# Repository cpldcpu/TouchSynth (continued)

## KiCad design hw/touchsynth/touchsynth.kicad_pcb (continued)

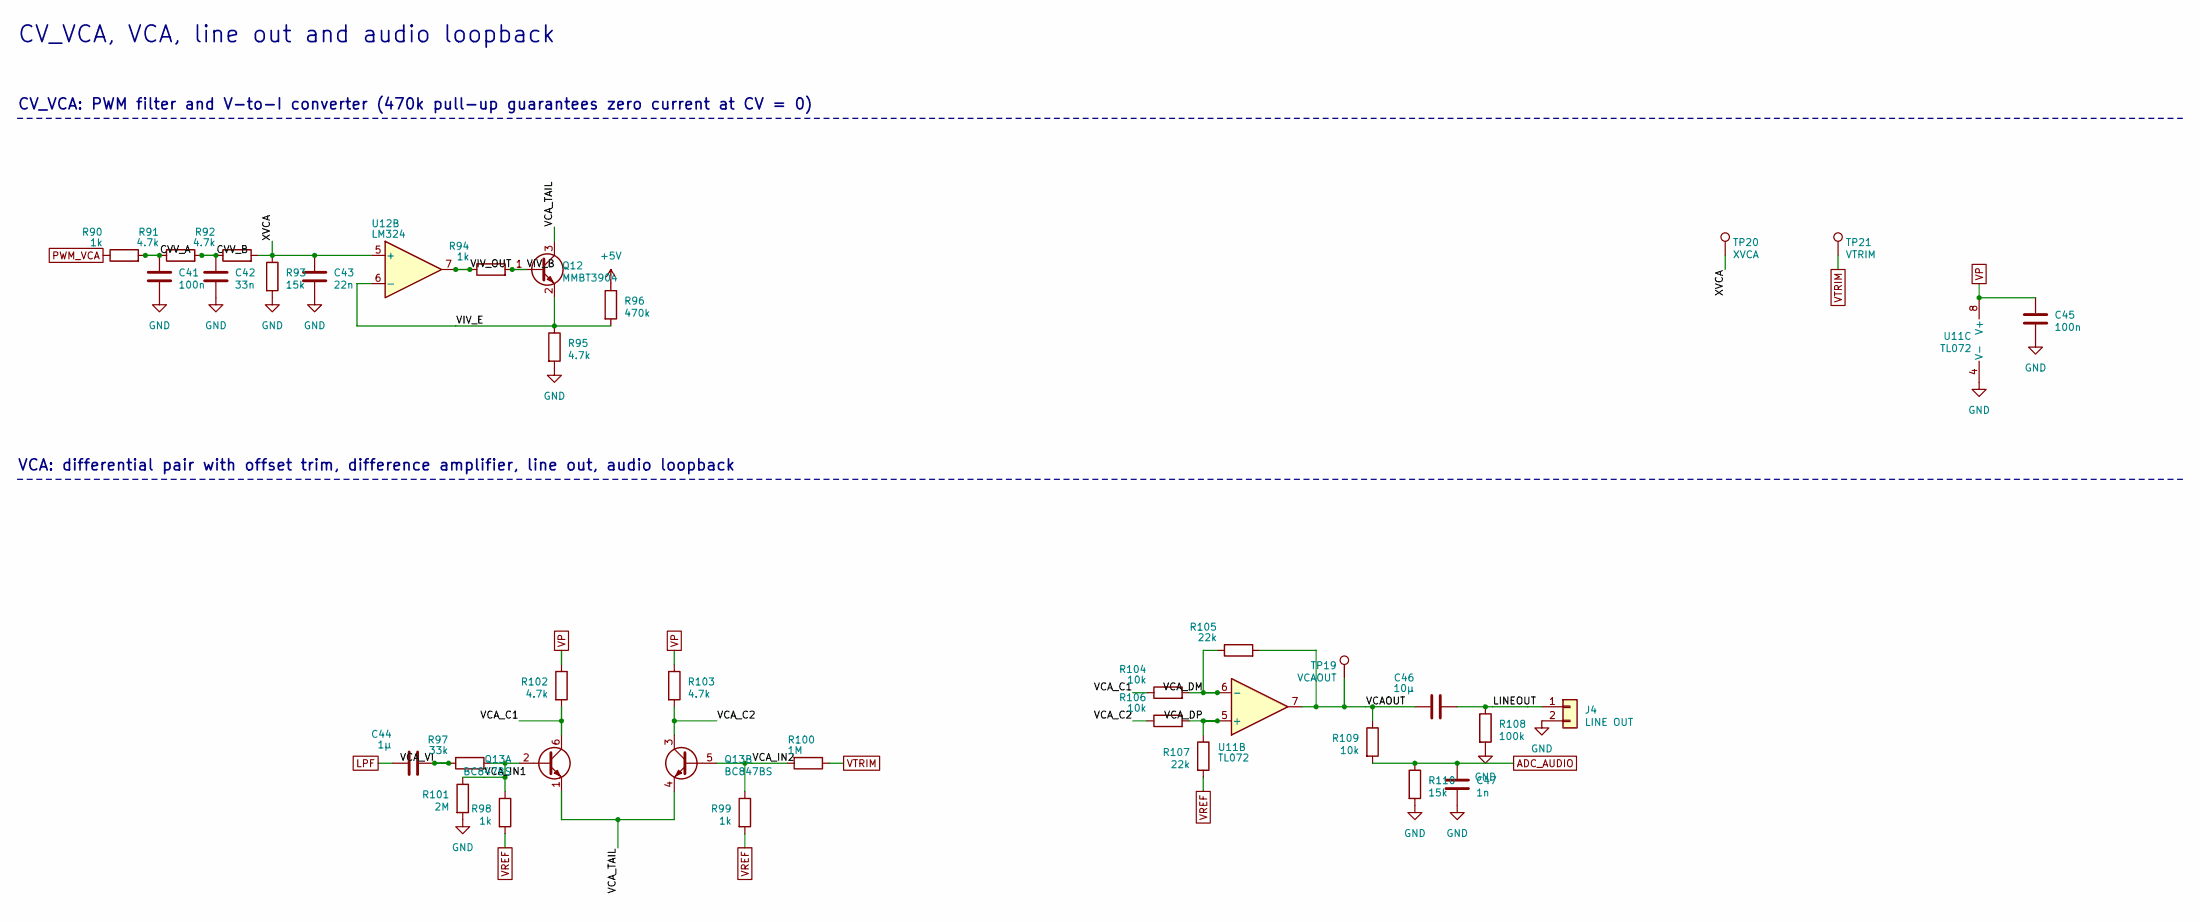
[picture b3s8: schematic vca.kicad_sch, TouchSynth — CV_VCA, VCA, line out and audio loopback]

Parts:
C41, C45: 100n; C_0603_1608Metric; LCSC C14663
C42: 33n; C_0603_1608Metric; LCSC C21117
C43: 22n; C_0603_1608Metric; LCSC C21122
C44: 1µ; C_0603_1608Metric; LCSC C15849
C46: 10µ; C_0603_1608Metric; LCSC C19702
C47: 1n; C_0603_1608Metric; LCSC C1588
J4: LINE OUT; PinHeader_1x02_P2.54mm_Vertical
Q12: MMBT3904; SOT-23; LCSC C20526
Q13: BC847BS; SOT-363_SC-70-6; LCSC C41375126
R90, R94, R98, R99: 1k; R_0603_1608Metric; LCSC C21190
R91, R92, R95, R102, R103: 4.7k; R_0603_1608Metric; LCSC C23162
R93, R110: 15k; R_0603_1608Metric; LCSC C22809
R96: 470k; R_0603_1608Metric; LCSC C23178
R97: 33k; R_0603_1608Metric; LCSC C4216
R100: 1M; R_0603_1608Metric; LCSC C22935
R101: 2M; R_0603_1608Metric; LCSC C22976
R104, R106, R109: 10k; R_0603_1608Metric; LCSC C25804
R105, R107: 22k; R_0603_1608Metric; LCSC C31850
R108: 100k; R_0603_1608Metric; LCSC C25803
TP19: VCAOUT; TestPoint_Pad_D1.0mm
TP20: XVCA; TestPoint_Pad_D1.0mm
TP21: VTRIM; TestPoint_Pad_D1.0mm
U11: TL072; SOIC-8_3.9x4.9mm_P1.27mm; LCSC C6961
U12: LM324; SOIC-14_3.9x8.7mm_P1.27mm; LCSC C71035

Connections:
+5V: R96.1; also elsewhere on the board
/vca/CVV_A: C41.1, R90.2, R91.1
/vca/CVV_B: C42.1, R91.2, R92.1
/vca/LINEOUT: C46.2, J4.1, R108.1
/vca/VCAOUT: C46.1, R105.2, R109.1, TP19.1, U11.7
/vca/VCA_C1: Q13.6 (C1), R102.2, R104.1
/vca/VCA_C2: Q13.3 (C2), R103.2, R106.1
/vca/VCA_DM: R104.2, R105.1, U11.6 (-)
/vca/VCA_DP: R106.2, R107.1, U11.5 (+)
/vca/VCA_IN1: Q13.2 (B1), R97.2, R98.1, R101.1
/vca/VCA_IN2: Q13.5 (B2), R99.1, R100.2
/vca/VCA_TAIL: Q12.3 (C), Q13.1 (E1), Q13.4 (E2)
/vca/VCA_VI: C44.2, R97.1
/vca/VIV_B: Q12.1 (B), R94.2
/vca/VIV_E: Q12.2 (E), R95.1, R96.2, U12.6 (-)
/vca/VIV_OUT: R94.1, U12.7
/vca/XVCA: C43.1, R92.2, R93.1, TP20.1, U12.5 (+)
ADC_AUDIO: C47.1, R109.2, R110.1; also elsewhere on the board
GND: C41.2, C42.2, C43.2, C45.2, C47.2, J4.2, R93.2, R95.2, R101.2, R108.2, R110.2, U11.4 (V-); also elsewhere on the board
LPF: C44.1; also elsewhere on the board
PWM_VCA: R90.1; also elsewhere on the board
VP: C45.1, R102.1, R103.1, U11.8 (V+); also elsewhere on the board
VREF: R98.2, R99.2, R107.2; also elsewhere on the board
VTRIM: R100.1, TP21.1; also elsewhere on the board

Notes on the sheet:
CV_VCA, VCA, line out and audio loopback
CV_VCA: PWM filter and V-to-I converter (470k pull-up guarantees zero current at CV = 0)
VCA: differential pair with offset trim, difference amplifier, line out, audio loopback

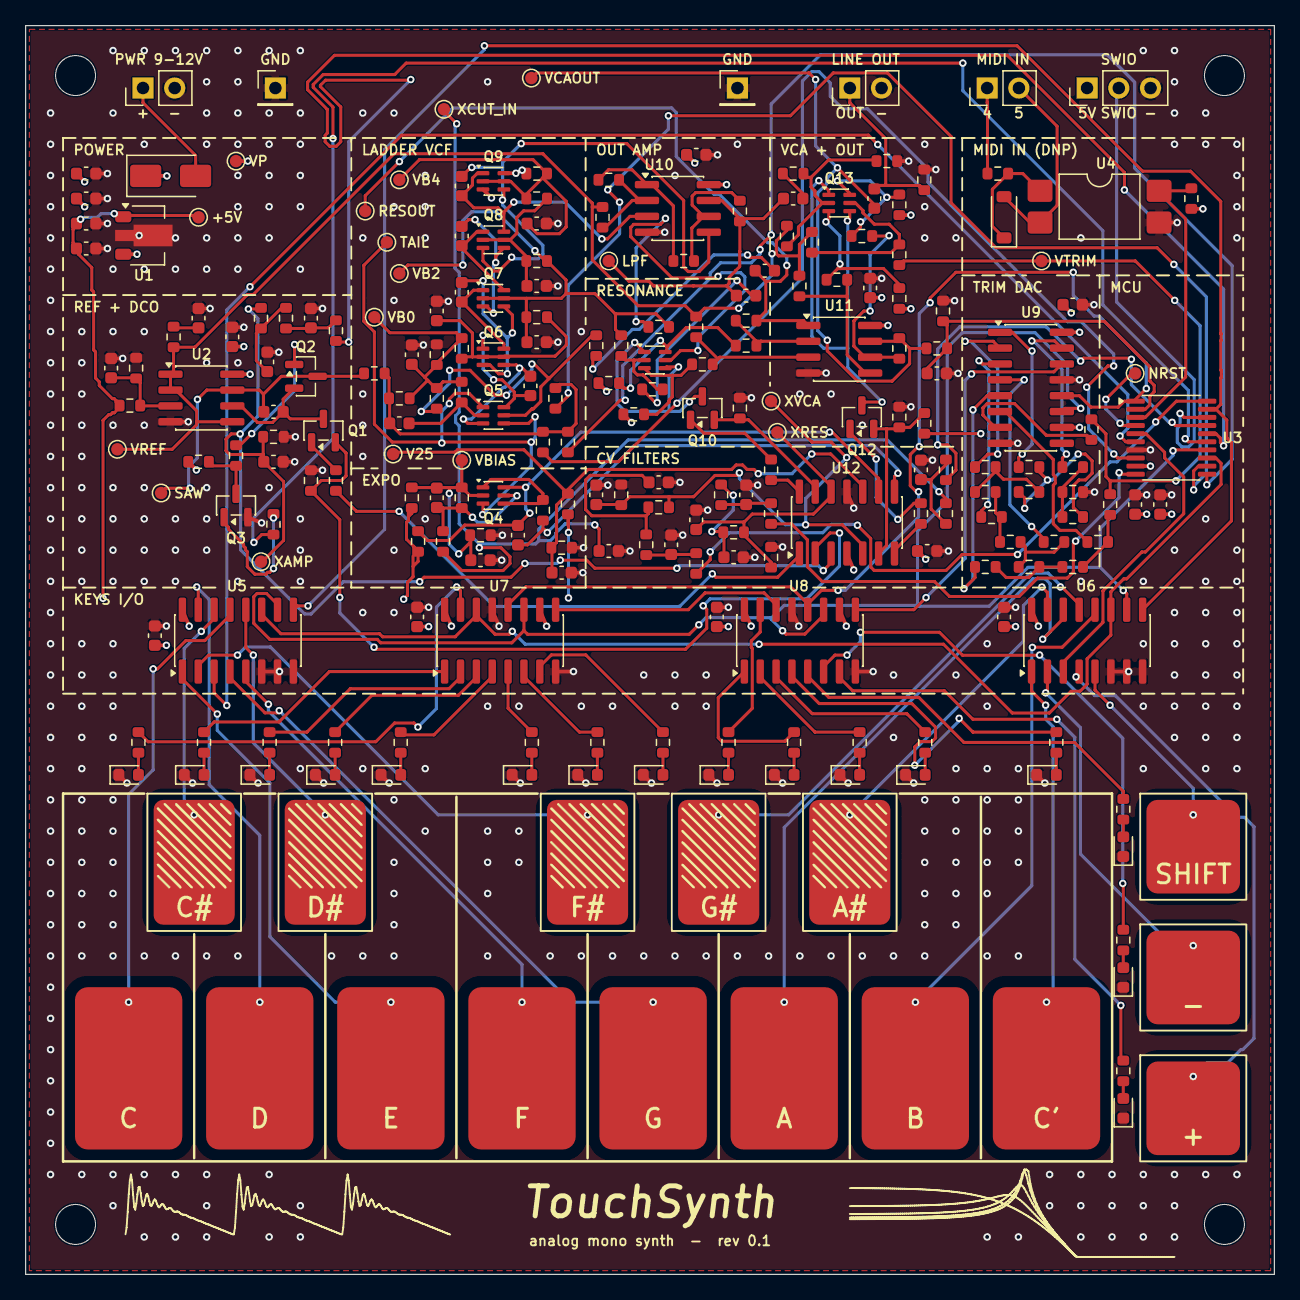
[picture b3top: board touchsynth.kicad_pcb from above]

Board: 4 copper layers, 100.0 x 100.0 mm, 246 parts (0 on the bottom side), 166 nets.

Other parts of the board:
H1, H2, H3, H4: M3; MountingHole_3.2mm_M3

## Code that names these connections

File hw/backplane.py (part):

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POWER = {"GND": "power:GND", "+5V": "power:+5V", "+3V3": "power:+3V3"}
RAIL = "+5V_IN"                                 # always a global label (input rail ahead of the slot rail)
FLAG_SHEETS = {"power": ("GND", "VBUS_C", "+5V_EXT", "+5V_IN", "+5V"),   # PWR_FLAGs: supplies no power-output
               "mcu": ("VDDA",), "mixer": ("VA_MIX",)}                 # pin drives (+3V3: LDO, VBUS_HOST: U4)
FLAGS = sum(FLAG_SHEETS.values(), ())
LAYOUTS = "layouts_backplane"                   # hand-drawn sheet layouts (power, mcu, bus, mixer)
SLOTS = 8
FX_SLOT = 1                    # the effects slot (pins 15 / 14 switchable to the mix sends, end of file)

SHEETS = OrderedDict([
    ("power", "Power entry, 3.3 V, soft start (option), USB-C device port, USB-A host port"),
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    pins = {}
    for k, (a, b) in enumerate(pairs):
        pins[1 + k], pins[8 - k] = a, b
    return add("RN", "Device:R_Pack04", value, FP["RN4"], pins, lcsc=lcsc, note=note)


def LED(color, a, k, note, **kw):
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

def HDR(ref, n, value, pins, note=None, dnp=False):
    return add("J", f"Connector_Generic:Conn_01x{n:02d}", value, FP[f"HDR{n}"], dict(enumerate(pins, 1)), ref=ref,
               bom=False, note=note, dnp=dnp)


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# =========================================================================== controller
sheet("mcu")
group("CH32V203C8T6 (assembled), decoupling, reset")
MCU = {1: "+3V3", 2: "SR_LATCH", 3: "SR_OE_N", 4: "PC15", 5: "OSC_IN", 6: "OSC_OUT", 7: "MCU_NRST", 8: "GND",
       9: "VDDA", 10: "ADC_L", 11: "ADC_R", 18: "PB0", 19: "CLK_O", 20: "LED_ACT", 21: "BCAST_O", 22: "RETURN",
       23: "GND", 24: "+3V3", 27: "PB14", 28: "VBUS_DET", 29: "SYNC_O", 30: "UART_TX", 31: "UART_RX",
       32: "USBD_DM", 33: "USBD_DP", 34: "SWDIO", 35: "GND", 36: "+3V3", 37: "SWCLK", 38: "FLASH_CS_N",
       39: "SPI_SCK", 40: "SPI_MISO", 41: "SPI_MOSI", 42: "USBH_DM", 43: "USBH_DP", 44: "BOOT0", 45: "HOST_EN",
       46: "HOST_FLT_N", 47: "GND", 48: "+3V3"}
SWIO_PIN = {1: 12, 2: 13, 3: 14, 4: 15, 5: 16, 6: 17, 7: 25, 8: 26}     # PA2 ... PA7, PB12, PB13
MCU.update({pin: f"SWIO_{k}" for k, pin in SWIO_PIN.items()})
add("U", "MCU_WCH_RiscV:CH32V203CxTx", "CH32V203C8T6", FP["LQFP48"], MCU, ref="U1", lcsc="C3001172",
    note="assembled by JLCPCB (C3001172, Extended; from the user's JLCPCB personal stock); SPI1 remap 1 (PA15/PB3/PB4/PB5); TIM3 CH4 (PB1) = 24 MHz CLK option")
for pin in (24, 36, 48):
    C(None, "100n", "+3V3", "GND", 3.3, note=f"MCU decoupling VDD pin {pin}")
C(None, "100n", "+3V3", "GND", 3.3, note="MCU decoupling VBAT")
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add("JP", "Jumper:Jumper_3_Open", "BOOT0", FP["HDR3"], {1: "+3V3", 2: "BOOT0", 3: "GND"}, ref="JP2", bom=False,
    note="1-2: system bootloader (USART1 / USB), open or 2-3: run from flash")
R(None, "10k", "BOOT0", "GND", note="BOOT0 low by default")
HDR("J6", 3, "UART", ("GND", "UART_TX", "UART_RX"), note="USART1: GND, TX (PA9), RX (PA10); 5 V adapters are fine (FT)")
group("MIDI DIN in (option, not fitted): opto into PA10 through JP3")
HDR("J7", 3, "MIDI IN", ("MIDI_4", "MIDI_5", "GND"), note="DIN pin 4, DIN pin 5, shield (panel jack on wires)",
    dnp=True)
R(None, "220", "MIDI_4", "MIDI_LA", dnp=True, note="MIDI loop series")
add("U", "Isolator:LTV-817S", "LTV-817S", FP["OPTO"], {1: "MIDI_LA", 2: "MIDI_5", 3: "GND", 4: "MIDI_RX"},
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R(None, "10k", "FLASH_CS_N", "+3V3", note="flash deselected while the MCU boots")
R(None, "10k", "FLASH_WP_N", "+3V3", note="flash WP idle")
R(None, "10k", "FLASH_HOLD_N", "+3V3", note="flash HOLD idle")
R(None, "10k", "LED_ACT", "GND", note="PB2 = BOOT1: low at reset")
R(None, "1k", "LED_ACT", "LED_ACT_A", note="activity LED series")
LED("yellow", "LED_ACT_A", "GND", "activity")
for n in ("PC15", "PB0", "PB14"):
    TP(n, note="free MCU pin")
for n in ("+3V3", "+5V", "GND"):
    TP(n)
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# other slot; a voice card grounds them, which these not-fitted positions ignore) into the line-out stage
# instead of the mix (loop-through: remove the line-out 220 R from MIX_L / MIX_R, fit the two below).
sheet("bus")
group("Effects slot 1: pins 15 / 14 = CLK / SWIO_1 or the mix sends; pins 3 / 4 = the loop-through return")
R(None, "0", "CLK", "FX_P15", note="effects slot: CLK to slot 1 pin 15 (remove for an effects card)")
R(None, "220", "MIX_L", "FX_P15", dnp=True, note="effects slot: send L to slot 1 pin 15 (fit for an effects card)")
R(None, "0", "SWIO_1", "FX_P14", note="effects slot: SWIO_1 to slot 1 pin 14 (remove for an effects card)")
R(None, "220", "MIX_R", "FX_P14", dnp=True, note="effects slot: send R to slot 1 pin 14 (fit for an effects card)")
R(None, "220", "FX_RET_L", "LO_L", dnp=True, note="effects slot: return L from slot 1 pin 3 to the line out (loop-through)")
R(None, "220", "FX_RET_R", "LO_R", dnp=True, note="effects slot: return R from slot 1 pin 4 to the line out (loop-through)")

# --------------------------------------------------------------------------- simulation cross-reference (S12 --bus2)
SIM_ONLY = {f"{e}{x}{s}_0".upper() for e in ("RO", "LO", "CC", "RBC") for x in "lr" for s in range(SLOTS)} | \
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
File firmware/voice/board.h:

/* TouchSynth board definition: pins from hw/design.py (MCU U3, TSSOP-20), remap codes per chip family.
 *
 *  pin port  net          use                         pin port  net          use
 *   1  PD4   LATCH        74HC595 RCLK (GPIO)          11  PC1   SUB          sub-oscillator (GPIO)
 *   2  PD5   ADC_AUDIO    ADC IN5 <- audio loopback    12  PC2   PULSE        TIM2 CH2
 *   3  PD6   MIDI_RX      USART1 RX                    13  PC3   S0_DATA      mux S0 / 595 SER
 *   4  PD7   NRST                                      14  PC4   S1_CLK       mux S1 / 595 SRCLK
 *   5  PA1   TOUCH_B      mux B common, ADC IN1        15  PC5   DCO_RST      TIM2 CH1 (active low)
 *   6  PA2   TOUCH_A      mux A common, ADC IN0        16  PC6   PWM_AMP      TIM1 CH1
 *   8  PD0   NOISE        noise (GPIO)                 17  PC7   PWM_CUT      TIM1 CH2
 *  10  PC0   PWM_RES      TIM1 CH3                     18  PD1   SWIO
 *                                                       19  PD2   S2           mux S2 (GPIO)
 *                                                       20  PD3   PWM_VCA      TIM1 CH4
 *
 * Timer remaps (checked against the CH32V003 reference header and the CH32V002 datasheet pin table):
 *   CH32V003: TIM1 partial remap 1 (01b): CH1 PC6, CH2 PC7, CH3 PC0, CH4 PD3
 *             TIM2 partial remap 1 (01b): CH1 PC5, CH2 PC2
 *   CH32V00x: TIM1_RM = 0010b: TIM1_CH1_2 PC6, TIM1_CH2_2 PC7, TIM1_CH3_2 PC0, TIM1_CH4_2 PD3
 *             TIM2_RM = 010b:  TIM2_CH1_ETR_2 PC5, TIM2_CH2_2 PC2
 * The complementary / break functions these remaps also route (TIM1 CH1N PC3, CH2N PC4, CH3N PD1, BKIN PC1,
 * TIM2 CH3 PD2) are never enabled; TIM2 CH4 on PC1 only in the dual-PWM DAC build (DAC_DUAL, hw.h).
 */
#ifndef BOARD_H
#define BOARD_H

#include "ch32fun.h"

#ifndef BOARD_CARD
#define BOARD_CARD 0                                   /* 1: the voice card (make BOARD=card), else board 1 */
#endif

#if BOARD_CARD
/* Voice card (hw/voice.py, docs/spec.md 3.2; TSSOP-20 pin numbers, the same port pins on any V006 package):
 *   PD4 SYNC_IN (EXTI)   PD5 TX_OUT (bus return)   PD6 RX_IN (bus)   PD0 LED_PLAY   PC3 LED_STAT
 *   PC6 TIM1 CH1 VCA trim   PC7 CH2 CV_CUT   PC0 CH3 CV_RES   PD3 CH4 CV_VCA   PC2 TIM2 CH2 DAC   PC1 TIM2 CH4 DAC low
 *   PC4 ADC A2 loopback   PA2 A0 / PD2 A3 self-test (option)   PA1 clock in (option)   PC5 spare
 * No DCO, no 74HC595: CV channel 0 is the VCA trim, hw_leds_dac() drives the two LEDs and the trim. */
#define PIN_SYNC     PD4
#define PIN_TX       PD5
#define PIN_MIDI_RX  PD6                               /* bus RX */
#define PIN_LED_PLAY PD0
#define PIN_LED_STAT PC3
#define PIN_CV_AMP   PC6                               /* CV channel 0: VCA trim on the card */
#define PIN_CV_CUT   PC7
#define PIN_CV_RES   PC0
#define PIN_CV_VCA   PD3
#define PIN_PULSE    PC2                               /* DAC */
#define PIN_SUB      PC1                               /* DAC low byte (dual PWM) */
#define PIN_AUDIO    PC4
#define ADC_CH_AUDIO 2
#else
#define PIN_LATCH    PD4
#define PIN_AUDIO    PD5
#define PIN_MIDI_RX  PD6
#define PIN_TOUCH_B  PA1
#define PIN_TOUCH_A  PA2
#define PIN_NOISE    PD0
#define PIN_CV_RES   PC0
#define PIN_SUB      PC1
#define PIN_PULSE    PC2
#define PIN_S0_DATA  PC3
#define PIN_S1_CLK   PC4
#define PIN_DCO_RST  PC5
#define PIN_CV_AMP   PC6
#define PIN_CV_CUT   PC7
#define PIN_S2       PD2
#define PIN_CV_VCA   PD3

#define ADC_CH_TOUCH_A 0
#define ADC_CH_TOUCH_B 1
#define ADC_CH_AUDIO   5
#endif

#if defined(CH32V003)
#define CHIP_NAME "CH32V003"
#define REMAP_MASK   (AFIO_PCFR1_TIM1_REMAP | AFIO_PCFR1_TIM2_REMAP)
#define REMAP_BITS   (AFIO_PCFR1_TIM1_REMAP_PARTIALREMAP1 | AFIO_PCFR1_TIM2_REMAP_PARTIALREMAP1)
#elif defined(CH32V00x)
#if defined(CH32V002)
#define CHIP_NAME "CH32V002"
#elif defined(CH32V006)
#define CHIP_NAME "CH32V006"
#else
#define CHIP_NAME "CH32V00x"
#endif
#define REMAP_MASK   (AFIO_PCFR1_TIM1_RM | AFIO_PCFR1_TIM2_RM)
#define REMAP_BITS   (AFIO_PCFR1_TIM1_RM_1 | AFIO_PCFR1_TIM2_RM_1)       /* TIM1_RM = 0010b, TIM2_RM = 010b */
#else
#error "unsupported MCU"
#endif

/* timer register bits (identical on both families; the vendor headers name them differently) */
#define T_CEN      0x0001
#define T_UDIS     0x0002
#define T_ARPE     0x0080
#define T_CMS2     0x0040   /* centre-aligned mode 2 (counts up and down, compare flags on the up-count only) */
#define T_UIE      0x0001
#define T_UIF      0x0001
#define T_UDE      0x0100   /* DMAINTENR: DMA request on update */
#define T_CC1DE    0x0200   /* DMAINTENR: CC1 DMA request */
#define T_CCDS     0x0008   /* CTLR2: the CCx DMA requests at the update event */
#define T_UG       0x0001
#define T_MOE      0x8000
#define T_OC_PWM1_LO  0x0068   /* OCxM = 110 (PWM1) + OCxPE, channel 1 / 3 half of CHCTLRx */
#define T_OC_PWM1_HI  0x6800   /* same for channel 2 / 4 */
#define T_OC_FRZ_LO   0x0008   /* OCxM = 000 (frozen: compare flag only) + OCxPE, channel 1 / 3 */
#define T_CC1E     0x0001
#define T_CC1P     0x0002
#define T_CC2E     0x0010
#define T_CC3E     0x0100
#define T_CC4E     0x1000

#define F_CPU      48000000UL
#define RESET_TICKS 144        /* DCO reset pulse: 3 us at 48 MHz (same as RESET_COUNTS in tables.h) */
#define CV_PWM_TOP 1023        /* TIM1: 10 bit at 46.875 kHz, 2 more bits by dithering */
#define FRAME_CYCLES 48000     /* HCLK cycles per 1 ms frame (SYNC period), nominal */
#ifndef BUS_BAUD
#define BUS_BAUD   1000000     /* card: voice bus (docs/bus.md 2): USART divider 48 = 3.0 (2 Mbaud: 24 = 1.5, exact) */
#endif
#ifndef BUS_TX_PP
#define BUS_TX_PP  0           /* 1: drive the return line push-pull during a reply (bench without pull-up, hw.c) */
#endif

/* interrupt state save / restore (mstatus.MIE only), usable in the control tick as well as in the main loop:
   ch32fun's __disable_irq / __enable_irq also clear / set MPIE, which inside a handler changes the state that mret
   restores */
static inline uint32_t irq_save(void)
{
	uint32_t s;
	__asm volatile(ADD_ARCH_ZICSR "csrrci %0, mstatus, 8" : "=r"(s) :: "memory");
	return s;
}

static inline void irq_restore(uint32_t s)
{
	if (s & 8)
		__asm volatile(ADD_ARCH_ZICSR "csrsi mstatus, 8" ::: "memory");
}

#endif

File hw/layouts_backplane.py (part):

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# drawn as global labels like the cross-sheet nets around them, so the label stacks stay uniform: on the bus sheet
# the bus nets at the slot sockets, on the MCU sheet the local nets at the controller and flash pins
GLOBAL = {"SYNC", "BCAST", "CLK", "FX_P14", "FX_P15", "FX_RET_L", "FX_RET_R"} | {f"NRST_{k}" for k in range(1, D.SLOTS + 1)} | \
    {"PC15", "PB0", "PB14", "LED_ACT", "BOOT0", "SPI_MISO", "FLASH_CS_N", "FLASH_WP_N", "FLASH_HOLD_N"}
PART = {p.ref: p for p in D.PARTS}


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

def tp(net, k=0):
    return [p.ref for p in D.PARTS if p.lib_id == "Connector:TestPoint" and p.pins["1"] == net][k]


def by(pred):
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def nets(**pins):
    """the part whose pins carry exactly these nets (pin number -> net), e.g. nets(_1="CC1", _2="GND")"""
    want = {k.lstrip("_"): v for k, v in pins.items()}
    return by(lambda p: p.pins == want)


def vcap(sh, r, x, ytop, gnd=True, fields="right"):
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    # ESD array on the connector side of the 0 R positions
    u3 = "U3"
    sh.place(u3, 76.2, 132.08, fields=(15.24, -13.97))
    for pin, net, d in ((1, "USBC_DM", (-1, 0)), (3, "USBC_DP", (-1, 0)), (4, "CC1", (1, 0)), (6, "CC2", (1, 0))):
        stub(sh, (u3, pin), d, net)
    vp = sh.P(u3, 5)
    sh.w(vp, (vp[0], vp[1] - U), (vp[0] + 7.62, vp[1] - U))
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    u5 = "U5"
    sh.place(u5, 177.8, yh + 17.78, fields=(-20.32, -10.16))
    sh.w((u5, 5), (177.8, yh))
    for pin, net in ((1, "USBH_DM"), (3, "USBH_DP")):
        stub(sh, (u5, pin), (-1, 0), net)
    sh.gnd((u5, 2))
    # D-, D+ pull-down options
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    vcap(sh, note("reset filter"), rs[0] - 17.78, yr)
    sh.text("RESET: the controller only; the 595", rs[0] - 50.8, yr + 20.32, 1.27, False)
    sh.text("outputs go off, the cards keep running", rs[0] - 50.8, yr + 24.13, 1.27, False)
    sh.text("SPI1 remap 1 (PA15, PB3, PB4, PB5); TIM3 CH4 (PB1) = 24 MHz CLK option", xm - 50.8, ym + 60.96, 1.27,
            False)

    # ---- crystal
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    sh.text("X50328MSB2GI: 20 pF load, 2 x 30 pF with the strays", 66.04, yy + 22.86, 1.27, False)

    # ---- MIDI DIN in (option)
    sh.heading("MIDI DIN in (option, not fitted): opto into PA10 through JP3", 15, 30, 137)
    X, Y = 83.82, 60.96
    sh.place("U9", X, Y, fields="above")
    sh.place("J7", 25.4, Y, mirror="y", fields="left")            # pins on the right
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    sh.lbl((clk[0] + 33.02, clk[1]), "SWCLK", (1, 0))
    v33(sh, stub_w(sh, sh.P("J5", 1), -U, horiz=True))
    sh.gnd(stub_w(sh, sh.P("J5", 4), -U, horiz=True))
    sh.text("J6 USART1: GND, TX (PA9), RX (PA10); 5 V adapters are fine (FT pins)", 289.56, 118.11, 1.27, False)
    sh.text("J5 WCH-LinkE: 3V3, SWDIO, SWCLK, GND", 289.56, 152.4, 1.27, False)
    # BOOT0 jumper
    yb0 = 177.8
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        r = nets(_1=net, _2="+3V3")
        sh.place(r, xp + i * 10.16, yp + 3.81, 180, fields="right")     # pin 2 (+3V3) up
        sh.lbl((r, 1), net, (0, 1), stub=U)
    # activity LED on PB2 (= BOOT1: pull-down)
    xl0, yl0 = 132.08, 215.9
    sh.lbl((xl0, yl0), "LED_ACT", (-1, 0))
    sh.w((xl0, yl0), (xl0 + 7.62, yl0))
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    sh.lbl((p[0] + 1.27, yl0), "LED_ACT_A", (1, 0))
    k = sh.P(d6, 1)
    sh.w(k, (k[0] + 5.08, yl0)); sh.gnd((k[0] + 5.08, yl0))
    sh.text("PB2 = BOOT1: low at reset", xl0 - 7.62, yl0 + 20.32, 1.27, False)
    # test points
    xt = 205.74
    for i, net in enumerate(("PC15", "PB0", "PB14")):
        x = xt + i * 15.24
        sh.place(tp(net), x, 220.98, fields="right")
        sh.lbl(sh.P(tp(net), 1), net, (0, 1), stub=U)
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    sh.text("33 R series at the driver; RETURN: the cards' TX are open drain", 20.32, 104.14, 1.27, False)

    # ---- effects slot: slot 1 pins 15 / 14
    sh.heading("Effects slot 1: pins 15 / 14 = CLK / SWIO_1 or the mix sends; pins 3 / 4 = loop-through return",
               15, 109.22, 150)
    fx = {p.pins["1"]: p.ref for p in D.PARTS if p.note and p.note.startswith("effects slot")}
    for k, (src, dst) in enumerate((("CLK", "FX_P15"), ("MIX_L", "FX_P15"), ("SWIO_1", "FX_P14"),
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        bus_row(sh, fx[src], x, 119.38 + 7.62 * k, src, dst)
    sh.text("effects card in slot 1: remove R79 / R81, fit R80 / R82 (the stereo mix to the card); loop-through:",
            20.32, 162.56, 1.27, False)
    sh.text("also remove the line-out 220 R from MIX_L / MIX_R (R71 / R75) and fit R83 / R84 (pins 3 / 4 to the line out)",
            20.32, 166.37, 1.27, False)

    # ---- NRST shift register
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    xu, yu = 60.96, 218.44
    sh.place(u6, xu, yu, fields=(-17.78, 15.24))
    xl = xu - 17.78                                               # input labels
    for pin, net in ((14, "SPI_MOSI"), (11, "SPI_SCK"), (12, "SR_LATCH"), (13, "SR_OE_N")):
        p = sh.P(u6, pin)
        sh.w(p, (xl, p[1]))
        sh.lbl((xl, p[1]), net, (-1, 0))
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        j = f"J{10 + k}"
        c = note(f"slot {k + 1} supply")
        socket(sh, j, c, 182.88 + (k % 4) * 60.96, 60.96 + (k // 4) * 55.88)
    sh.text("pins 1/2 +5V, 3/4/8/13/16 GND (slot 1: 3/4 the effects return); 5, 6, 7: the card's AUDIO_L, "
            "AUDIO_GND, AUDIO_R", 165.1, 140.97, 1.27,
            False)

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

def supply(sh, u, x, y, cap, label=True):
    """op-amp supply unit: V+ up (VA_MIX label, or the caller's wire), GND on V-, decoupling cap to the right"""
    sh.place(u, x, y, unit=3, fields=(-15.24, -1.27))
    vp, vm = sh.P(u, 8), sh.P(u, 4)
    if label:
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
def cell(sh, s, x, yln, yrn):
    """mixer cell of slot s + 1: AUDIO_L (top) into the SUM_LN bus at yln, AUDIO_R (bottom) into the SUM_RN bus at
    yrn, the AUDIO_GND mirror (C_G at x + 10.16) to the SUM_LP / SUM_RP labels"""
    k = s + 1
    yt = yln - 27.94                                              # top labels
    sh.lbl((x, yt), f"AUDIO_L_{k}", (0, -1))
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    for r, y, net in ((f"RPl{s}_0", yln - 12.7, "SUM_LP"), (f"RPr{s}_0", yln - 5.08, "SUM_RP")):
        p = hpart(sh, ref(r), xg, y, fields=(-1.27, -4.45))
        sh.lbl(p, net, (1, 0), stub=U)
    vup(sh, ref(f"RIr{s}_0"), x, yrn + 7.62)                      # pin 2 on the SUM_RN bus
    sh.w((x, yrn + 7.62), (x, yrn + 12.7))
    sh.lbl((x, yrn + 10.16), f"MXR_{k}", (1, 0))
    vup(sh, ref(f"CINr{s}_0"), x, yrn + 20.32)
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    s_ = sh.P("J3", "S")
    sh.w(s_, (s_[0] - U, s_[1]), (s_[0] - U, s_[1] + 5.08))
    sh.gnd((s_[0] - U, s_[1] + 5.08))
    sh.text("ADC dividers at the MCU pins (PA0, PA1): 0.64 x MIX", 322.58, yb + 38.1, 1.27, False)

    # ---- op-amp rail, VREF
    sh.heading("Op-amp rail and VREF 2.41 V (divider from the controller's +3V3, two RC stages, unbuffered)", 15, 193.04,
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
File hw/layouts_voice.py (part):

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

def tp(net, k=0):
    return [p.ref for p in D.PARTS if p.lib_id == "Connector:TestPoint" and p.pins["1"] == net][k]


def dec(u):
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

def nets(**pins):
    """the part whose pins carry exactly these nets (pin number -> net), e.g. nets(_1="RX", _2="RX_IN")"""
    want = {k.lstrip("_"): v for k, v in pins.items()}
    return by(lambda p: p.pins == want)


def vcap(sh, r, x, ytop, gnd=True, fields="right"):
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    sh.w((vdd[0], yv), (vdd[0] + 20.32, yv))
    vcap(sh, note("MCU decoupling"), vdd[0] + 10.16, yv)
    vcap(sh, note("MCU bulk"), vdd[0] + 20.32, yv)
    sh.text("PWM_PAN (PC5, TIM2 CH1): pan bias, vca sheet", 20.32, 132.08, 1.27, False)
    sh.text("TIM1_RM 0010 (CH1...CH4 = PC6, PC7, PC0, PD3), TIM2_RM 010 (CH1 = PC5, CH2 = PC2, CH4 = PC1)", 20.32,
            135.89, 1.27, False)
    sh.text("USART1 default (TX PD5 open drain, RX PD6); PA4 is bonded to PD7 (NRST): never an output", 20.32,
            139.7, 1.27, False)

    # ---- backplane connector
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    sh.lbl((xb + 38.1, y), "NRST", (1, 0))
    vcap(sh, note("NRST filter (option)"), xb + 12.7, y)
    tpx(sh, "NRST", (xb + 22.86, y))
    sh.text("RX idle high and SYNC low when unplugged (standalone detection); TX: PD5 open drain, pull-up on the "
            "backplane", xb - 7.62, 124.46, 1.27, False)

    # ---- programming and line out
    sh.heading("Programming (WCH-LinkE) and line out", 15, 150, 150)
    j2 = by(lambda p: p.value == "SWIO")
    y = 175.26
    sh.place(j2, 33.02, y, mirror="y", fields="left")              # pins on the right: +5V_PRG, SWIO, GND
    p1, p2, p3 = sh.P(j2, 1), sh.P(j2, 2), sh.P(j2, 3)
    sh.w(p1, (p1[0] + 20.32, p1[1])); sh.lbl((p1[0] + 20.32, p1[1]), "+5V_PRG", (1, 0))
    sh.w(p2, (p2[0] + 20.32, p2[1])); sh.lbl((p2[0] + 20.32, p2[1]), "SWIO", (1, 0))
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            sh.lbl(b1_, f"VB{k}", (-1, 0), stub=U)
            sh.lbl(b2_, f"VB{k}", (1, 0), stub=U)
            pq = ref(stages[k - 1])
            pc1, pc2 = sh.P(pq, 6), sh.P(pq, 3)
            sh.w(pc1, e1_); sh.w(pc2, e2_)
            yc = (pc1[1] + e1_[1]) / 2
            cc = ref(caps[k - 1])
            sh.place(cc, (pc1[0] + pc2[0]) / 2, yc, 90, fields="above")
            sh.w((pc1[0], yc), (cc, 1)); sh.w((cc, 2), (pc2[0], yc))
        if k == 4:
            va(sh, sh.P(q, 6)); va(sh, sh.P(q, 3))
    # top nodes N4A / N4B to the instrumentation amplifier
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

def pair_core(sh, sim, x, y, rc1, rc2, c_net, tail, cin, rin, rb1, rb2, bias, in_net, ri_net, gap=25.4, f2=None):
    """differential pair with emitters to the tail label; collector resistors to VA and collector labels
    c_net % 1|2 (rc1 = None: collectors left open, for a stacked stage); base 1: LPF -> cin -> rin -> base, both
    bases biased through rb1 / rb2. Returns (pins, base-1 drop x)."""
    q, P = pair(sh, sim, x, y, gap, f2)
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    tpx(sh, "VTRIM", (p[0] + 12.7, y))
    sh.lbl((p[0] + 22.86, y), "VTRIM", (1, 0))

    # ---- pan bias: PAN_B = VREF + p, p from the PC5 PWM through a passive network (S13 variant A)
    sh.heading("Pan bias (PC5, TIM2 CH1): PAN_B = VREF -143...+149 mV, 66 Hz", 270, 76.2, W)
    yn = 96.52
    sh.lbl((x0, yn), "PWM_PAN", (-1, 0))
    p = hpart(sh, ref("RPB"), x0, yn)
    sh.w(p, (p[0] + 43.18, yn))
    rpa, rpc = ref("RPA"), ref("RPC")
    sh.place(rpa, p[0] + 7.62, yn - 3.81, fields="left")         # pin 1 (VREF) up, pin 2 on the PAN_B line
    sh.lbl((rpa, 1), "VREF", (0, -1), stub=U)
    sh.place(rpc, p[0] + 17.78, yn - 3.81, fields="right")
    v33(sh, (rpc, 1), stub=U)
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    sh.place(rtrf, xd - 10.16, b1[1] + U + 3.81, 0, fields="left"); sh.gnd((rtrf, 2))
    xt = b2[0] + 10.16
    sh.w((xt, b2[1]), (xt + 5.08, b2[1]))
    hpart(sh, rtrm, xt + 5.08, b2[1], flip=True)                    # pin 2 (base side) left, pin 1 (VTRIM) right
    sh.lbl(sh.P(rtrm, 1), "VTRIM", (1, 0), stub=U)
    # steering pairs, emitters on the VCA collectors; loads 4.7k to VA, collector labels to the difference amps
    for k, sim, c in ((1, "QSL1", P[6]), (2, "QSL2", P[3])):
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    sh.lbl((p[0] + 17.78, out[1]), "AUDIO_L", (1, 0))
    sh.text("to the line-out header and J1 pin 5 (mcu)", p[0] - 10.16, out[1] - 12.7, 1.27, False)
    supply(sh, u, 3, 386.08, 172.72, dec(u))
    # loopback divider to PC4
    xl = out[0] + 12.7
    sh.heading("Audio loopback to PC4 (ADC A2)", xl + 5.08, 172.72, 360)
    rlb1, rlb2, clb = ref("RLB1"), ref("RLB2"), ref("CLB")
    sh.w((xl, out[1]), (xl, 180.34))
    sh.place(rlb1, xl, 180.34 + 3.81, fields="left")
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    sh.w((xl, out[1]), (xl, out[1] + 7.62))
    sh.place(rlb3, xl, out[1] + 7.62 + 3.81, fields="right")
    sh.lbl((rlb3, 2), "ADC_AUDIO", (0, 1), stub=U)
    sh.text("DNP option: L + R summed at PC4", xl + 5.08, out[1] + 20.32, 1.27, False)
    # spare unit B: follower on VREF (defined state), supply
    ip, o = follower(sh, u, 2, 241.3, 233.68 + U, (5, 6, 7))
    sh.lbl(ip, "VREF", (-1, 0), stub=5.08)
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
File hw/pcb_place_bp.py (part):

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Pre-routes (gen_pcb_bp.py, locked before Freerouting), all on F.Cu unless noted:
- +5 V: trunk down the east margin (x = 97.8, 1.0 mm) from the soft-start bypass, past the two bulk capacitors,
  rail along y = RAIL_Y (0.4 mm) to the mixer, one stub per socket pin 1 / 2 and per slot capacitor.
- voice bus inside the socket field, one track per gap between pin positions (backplane.md 7.3): SYNC gap 4|5,
  BCAST 5|6, RETURN 6|7, CLK 7|8, each with a short jog to its pin.
- audio fan-out per slot: AUDIO_L (pin 5) and AUDIO_R (pin 7) south outside the west row, AUDIO_GND (pin 6)
  between the rows, into the 0805 input capacitors that straddle the rail; on to the 56k resistors and through a
  via each onto the summing band.
- summing band on B.Cu (y 86.75 ... 91.95): L-, L+ | R+, R- with GND guard tracks; bottom pour kept out of it.
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
def gap_y(n):
    """y of the gap between socket pin positions n and n + 1"""
    return PIN1_Y - 2.54 * (n - 0.5)


def pin_xy(k, n):
    """socket pin n of slot k"""
    x = SLOT_X[k - 1] + (-1.27 if n % 2 else 1.27)
    return x, PIN1_Y - 2.54 * ((n + 1) // 2 - 1)


MX, MY = 52.0, 24.4                              # the MCU in the middle of the controller strip
BUS_GAP = {"SYNC": (4, 9), "BCAST": (5, 10), "RETURN": (6, 11), "CLK": (7, 15)}    # net -> (gap, pin)

# per-slot parts: note suffix -> (dx from the socket centre, y, rotation); the 0805 / 0603 pad 1 faces north at 270
SLOT_PARTS = {
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FX_PARTS = {                                             # (block, row, column 0 voice / 1 effects) -> part
    ("send", 0, 0): lambda p: p.note == "effects slot: CLK to slot 1 pin 15 (remove for an effects card)",
    ("send", 0, 1): lambda p: p.note == "effects slot: send L to slot 1 pin 15 (fit for an effects card)",
    ("send", 1, 0): lambda p: p.note == "effects slot: SWIO_1 to slot 1 pin 14 (remove for an effects card)",
    ("send", 1, 1): lambda p: p.note == "effects slot: send R to slot 1 pin 14 (fit for an effects card)",
    ("out", 0, 0): lambda p: p.pins == {"1": "MIX_L", "2": "LO_L"},
    ("out", 0, 1): lambda p: p.note and p.note.startswith("effects slot: return L"),
    ("out", 1, 0): lambda p: p.pins == {"1": "MIX_R", "2": "LO_R"},
    ("out", 1, 1): lambda p: p.note and p.note.startswith("effects slot: return R"),
}
FX_PLACES = [((FX_COLS[blk][col], FX_ROWS[row], 0 if col == 0 else 180), pred)
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    "CH32V203C8T6 (assembled), decoupling, reset": "mcu",
    "8 MHz crystal (PLL x 18 = 144 MHz)": "mcu",
    "Programming: SWD (WCH-LinkE), BOOT0, USART1 (bootloader, debug)": "mcu",
    "MIDI DIN in (option, not fitted): opto into PA10 through JP3": "midi",
    "SPI flash (footprint only), activity LED, free pins": "flash",
    "Bus drivers: broadcast, return, SYNC, 24 MHz clock (option)": "bus",
    "NRST: 74HC595 drives each card's NRST directly (outputs off at reset: the cards run freely)": "nrst",
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    "Line out (3.5 mm stereo) and ADC taps (USB audio)": "lineout",
}
NOTE_BLOCK = {"VREF": "vref", "power LED series": "leds", "activity LED series": "leds", "fault LED series": "host",
              "host power LED series": "host", "PB2 = BOOT1": "mcu", "ADC": "adc", "VBUS sense": "usbc",
              "free MCU pin": "tps"}
TP_BLOCK = {"+3V3": "power", "+5V": "power", "GND": "power", "SYNC": "bus", "BCAST": "bus", "RETURN": "bus",
            "VREF": "vref", "MIX_L": "mixc", "MIX_R": "mixc"}
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    if p.note in DEC:
        return DEC[p.note][1]
    if p.note == "crystal load":
        return {"OSC_IN": "1", "OSC_OUT": "2"}[p.pins["1"]]
    return None


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    if p.lib_id == "Connector:TestPoint":
        if p.note == "free MCU pin":
            return "tps"
        return TP_BLOCK.get(p.pins["1"], "mcu" if p.sheet == "mcu" else None)
    if p.sim and p.sim[:3] in ("RA1", "RA2") or (p.sim or "").startswith("CA"):
        return "adc"                              # ADC dividers at the MCU (backplane.md 5)
    for k, b in NOTE_BLOCK.items():
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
